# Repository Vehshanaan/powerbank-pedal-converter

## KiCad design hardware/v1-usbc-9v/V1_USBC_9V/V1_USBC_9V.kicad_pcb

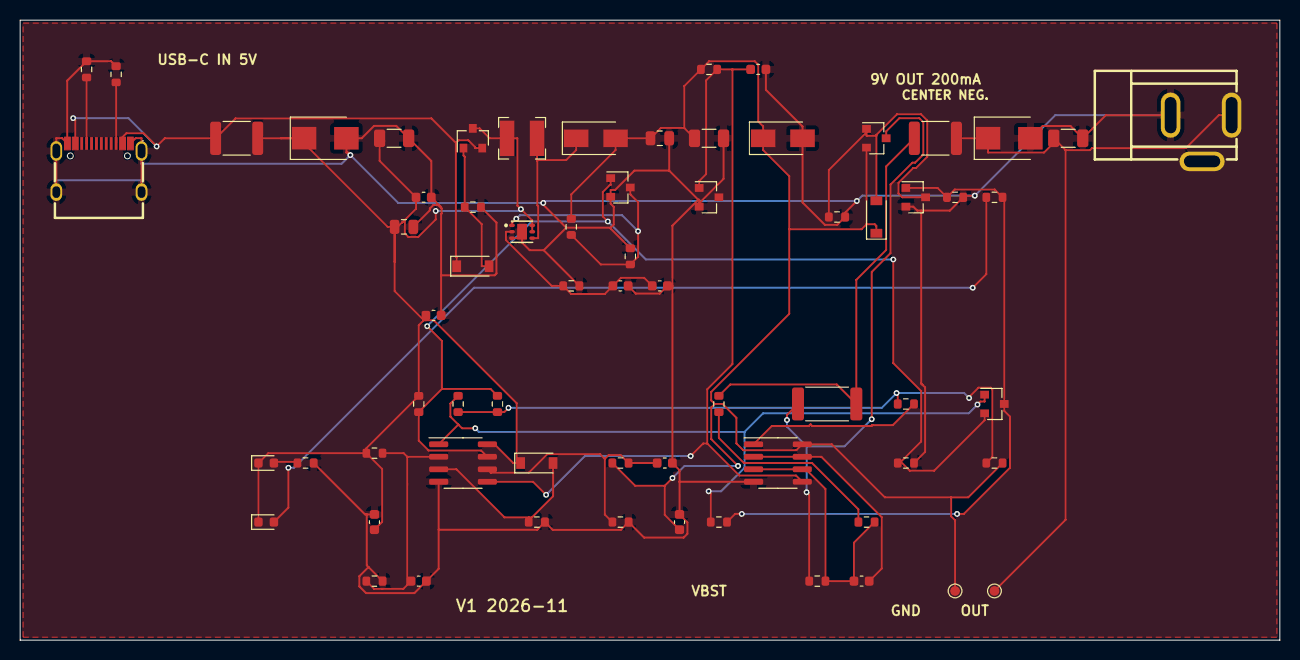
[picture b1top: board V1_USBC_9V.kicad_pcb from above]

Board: 2 copper layers, 128.0 x 63.0 mm, 67 parts (0 on the bottom side), 28 nets.

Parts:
C1, C6: 22uF; C_1206_3216Metric
C2, C4, C9, C10, C11, C13, C14: 100nF; C_0603_1608Metric
C3, C5: 4.7uF; C_0805_2012Metric
C7: 680pF; C_0603_1608Metric
C8: 10pF; C_0603_1608Metric
C12: 10nF; C_0603_1608Metric
C15: 47uF; C_1206_3216Metric
D1: SMBJ5.0A; D_SMB
D2: BZT52C10; D_SOD-123
D3: SS34; D_SMA
D4: BZT52C4V3; D_SOD-123
D5: BZT52C8V2; D_SOD-123
D6: SMAJ12A; D_SMA
D7: SMBJ12A; D_SMB
D8: BAT54S; SOT-23
D9: LED_GREEN; LED_0603_1608Metric
D10: LED_RED; LED_0603_1608Metric
F1: 500mA; Fuse_1812_4532Metric
F2: 200mA; Fuse_1812_4532Metric
J1: TYPE-C-31-M-12; USB-C_SMD-TYPE-C-31-M-12_1
J2: DC-005-5.5x2.1; DC-IN-TH_DC005
L1: 10uH; L_Bourns-SRN4018
Q1, Q2: AO3401A; SOT-23
Q3, Q6: MMBT3904; SOT-23
R1, R2: 5.1k; R_0603_1608Metric
R3, R8, R9, R13, R14, R15, R21, R23: 100k; R_0603_1608Metric
R4: 20k; R_0603_1608Metric
R5: 127k; R_0603_1608Metric
R6, R7, R10, R20, R24, R25, R28: 10k; R_0603_1608Metric
R11: 220k; R_0603_1608Metric
R12: 62k; R_0603_1608Metric
R16: 0.02; R_2512_6332Metric
R17, R19, R27: 1k; R_0603_1608Metric
R18: 27k; R_0603_1608Metric
R26: 4.7k; R_0603_1608Metric
TP1: TEST_VBST; TestPoint_Pad_D1.0mm
TP2: TEST_OUT; TestPoint_Pad_D1.0mm
U2: TPS61170DRVR; QFN-6_L2.0-W2.0-P0.65-TL-EP
U3: LM4040C25; SOT-23
U4, U6: LM2903A; SOIC-8_3.9x4.9mm_P1.27mm

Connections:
CC1: J1.A5, R1.1
CC2: J1.B5, R2.1
COMP: C7.1, C8.1, R6.1, U2.2
EN: R14.1, R15.1, R20.1, R25.1
FB: Q6.3, R4.1, R5.1, U2.1
GATE1: D2.2, Q1.1, R3.1
GATE2: D5.2, Q2.1, Q3.3, R21.1
GND: C1.2, C2.2, C3.2, C4.2, C5.2, C6.2, C7.2, C8.2, C9.2, C10.2, C11.2, C12.2, C13.2, C15.2, D1.2, D6.2, D7.2, J1.1, J1.2, J1.3, J1.4, J1.A1B12, J1.B1A12, J2.2, Q3.2, Q6.2, R1.2, R2.2, R3.2, R4.2, R6.2, R9.2, R10.2, R12.2, R21.2, R23.2, R26.2, R28.2, U2.3, U2.7, U3.2, U4.4, U6.4
LEDG: D9.2, R26.1
LEDR: D10.2, R27.1
OC: R20.2, U6.1
OCN: R17.1, R18.1
OCP: C14.1, R18.2, R19.2, U6.3, U6.6
OCREF: C14.2, U6.2, U6.7
OV: D8.2, Q6.1, R13.1, R15.2, R28.1, U4.7
OVP: C12.1, R11.2, R12.1, U4.6
PEDAL: F2.1, R16.2, R17.2
PEDAL_OUT: C15.1, D7.1, F2.2, J2.1, TP2.1
Q2D: Q2.3, R16.1, R19.1
Q3B: D8.3, Q3.1, R23.1, R24.2, R27.2
SW: D3.1, L1.2, U2.4
UV: D8.1, R14.2, R24.1, U4.1
UVP: C11.1, R8.2, R9.1, U4.2
UVREF: D4.2, R10.1, U4.3
VBST: C5.1, C6.1, C13.1, D3.2, D5.1, D6.1, Q2.2, R5.2, R7.1, R11.1, R25.2, TP1.1, U6.8
VBUS: D2.1, F1.1, J1.A4B9, J1.B4A9, Q1.2
VIN: C1.1, C2.1, C3.1, C4.1, C10.1, D1.1, D4.1, D9.1, D10.1, F1.2, L1.1, Q1.3, R8.1, R13.2, U2.5, U2.6, U4.8
VREF: C9.1, R7.2, U3.1, U4.5, U6.5
